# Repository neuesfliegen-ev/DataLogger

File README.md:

# 🛩️ Flight Data Logger

This project is a **Flight Data Logger** designed for UAVs and model aircraft. It logs sensor and GPS data at 1 Hz to an SD card in CSV format and streams live telemetry to a server over a cellular (3G/4G) link. The system uses an IMU, a barometric sensor and a GPS module, and shows live status updates on an OLED screen.

## 📦 Features

- Logs data to SD card in `.csv` format
- Captures:
  - 9-axis IMU data (acceleration, gyroscope, magnetometer)
  - Barometric pressure, altitude and temperature
  - GPS coordinates, altitude, speed and satellite count
- OLED display for live status updates
- **Live telemetry over cellular**: an ESP32 gateway forwards data to a web server through a SIM7600 modem (see [Live Telemetry](#-live-telemetry-esp32--sim7600))
- Live dashboard for the telemetry data
- Modular and extensible design for future sensor integration

## 🧠 Core Components

| Component           | Description |
|---------------------|-------------|
| **Arduino**         | Primary microcontroller (Nano 33 BLE Sense REV2): sensors, SD logging, OLED |
| **ESP32**           | Telemetry gateway between the Arduino and the cellular modem |
| **SIM7600**         | Cellular modem (with SIM card), controlled by AT commands over UART |
| **BMI270_BMM150**   | 9-DOF IMU (acceleration, gyroscope, magnetometer) |
| **LPS22HB**         | Barometric pressure sensor |
| **TinyGPS++**       | GPS data parser |
| **SH1106 OLED**     | I2C 128x64 screen for live feedback |
| **SD Card Module**  | Stores `.csv` data logs |
| **Voltage Divider** | Scales down battery voltage for safe ADC reading |

---

## 📡 Live Telemetry (ESP32 + SIM7600)

Code: [`esp32SimNano.ino`](esp32SimNano.ino)

```
Arduino Nano ──I2C (JSON frames)──► ESP32 ──UART (AT commands)──► SIM7600 ──HTTP POST──► Server ──► Dashboard
     ▲                                │
     └────── READY / ACK (GPIO) ──────┘
```

- **Arduino → ESP32:** the ESP32 runs as an I2C slave (address `0x42`) and receives each data frame as a JSON payload.
- **Handshake:** two GPIO lines coordinate the transfer:
  - `READY` (ESP32 → Nano, GPIO 4): high when the modem is up and the ESP32 can accept a new frame.
  - `ACK` (ESP32 → Nano, GPIO 5): high when the last frame was delivered successfully (HTTP 200).
- **ESP32 → SIM7600:** UART2 at 115200 baud (ESP32 TX = GPIO 17, RX = GPIO 16). On startup the ESP32:
  1. waits until the modem answers `AT`
  2. disables echo (`ATE0`)
  3. opens the network (`AT+NETOPEN`)
  4. starts an HTTP session (`AT+HTTPINIT`, recovering with `AT+HTTPTERM` if a session is stuck)
  5. sets the server URL and `application/json` content type (`AT+HTTPPARA`)
- **Sending:** each frame is uploaded with `AT+HTTPDATA` and sent as an HTTP POST (`AT+HTTPACTION=1`). The ESP32 then waits for an HTTP 200 response.
- **Health check:** the ESP32 polls the modem with `AT` every 200 ms and updates the `READY` line.
- **Modes:** the payload carries a `"mode"` field (`REALTIME` or `BATCH`), which the ESP32 parses.

---

## 🔧 Circuit Diagram

[Wiring diagram](Datenlogger_Files/Datalogger_schematic%20v2.pdf)

> Note: the schematic still shows a 430 Ω resistor in the voltage divider. Use **510 Ω** as described below.

---

## 🔋 ADC Voltage Divider

To safely read the battery voltage with the Arduino's 3.3 V ADC pin, use the following voltage divider:

- **Input voltage**: up to 4.2 V (LiPo 1S max)
- **Top resistor (battery side)**: 510 Ω
- **Bottom resistor (to GND, ADC reads across it)**: 1.8 kΩ

### 📐 Voltage Divider Calculation

```
Vout = Vin × R_bottom / (R_top + R_bottom)
     = 4.2 V × 1800 / (510 + 1800)
     ≈ 3.27 V
```

---

## 📂 Data Format

Logged data is stored as a CSV file (`log.csv`) with the following headers:

```
timestamp,accX,accY,accZ,gyroX,gyroY,gyroZ,magX,magY,magZ,
latitude,longitude,gpsAltitude,Speed,SatCount,roll,pitch,yaw,
pressure,temperature,paltitude
```

Example row:

```
1542,-0.01,0.02,9.81,0.01,-0.02,0.00,30.12,11.23,-45.66,
52.5200,13.4050,120.5,10.4,9,0,0,0,100.3,25.5,132.2
```

---

## 🛠️ Getting Started

### 🔌 Wiring

- Connect sensors and modules via I2C/SPI/Serial as per the diagram.
- Ensure GPS is connected to `Serial1` (typically `TX`/`RX` on the Arduino). (IMPORTANT)
- For telemetry: connect the Arduino to the ESP32 over I2C plus the `READY`/`ACK` lines, and the ESP32 to the SIM7600 over UART (pins above). Insert an active SIM card.
- Insert a **FAT32-formatted SD card**.

### 🧪 Uploading

1. Install dependencies (Arduino):
   - `Arduino_BMI270_BMM150`
   - `Arduino_LPS22HB`
   - `TinyGPSPlus`
   - `U8g2`
2. Compile and upload the main sketch to the Arduino.
3. Upload `esp32SimNano.ino` to the ESP32 (ESP32 board package, uses `Wire` and `HardwareSerial`). Set the server URL in `initSIM7600()` if needed.
4. Open the Serial Monitor at **115200 baud** to see real-time debug info (the ESP32 also echoes modem responses there).

---

## 📊 OLED Display

The OLED shows system status:
- Sensor initialization
- GPS satellite count
- Errors during SD or sensor setup
- Team number

> To keep the display clear and reduce power, messages are brief and limited to startup and GPS updates.

---

## 🧩 Planned Improvements

- Add orientation calculation (roll, pitch, yaw)
- Support logging at configurable rates (5 Hz, 10 Hz)
- Add battery voltage and current sensors

---

## 👨‍💻 Credits

- Developed by the **Neues Fliegen Avionics Team**
- Based on libraries by Arduino, Adafruit and Mikal Hart (TinyGPS++)

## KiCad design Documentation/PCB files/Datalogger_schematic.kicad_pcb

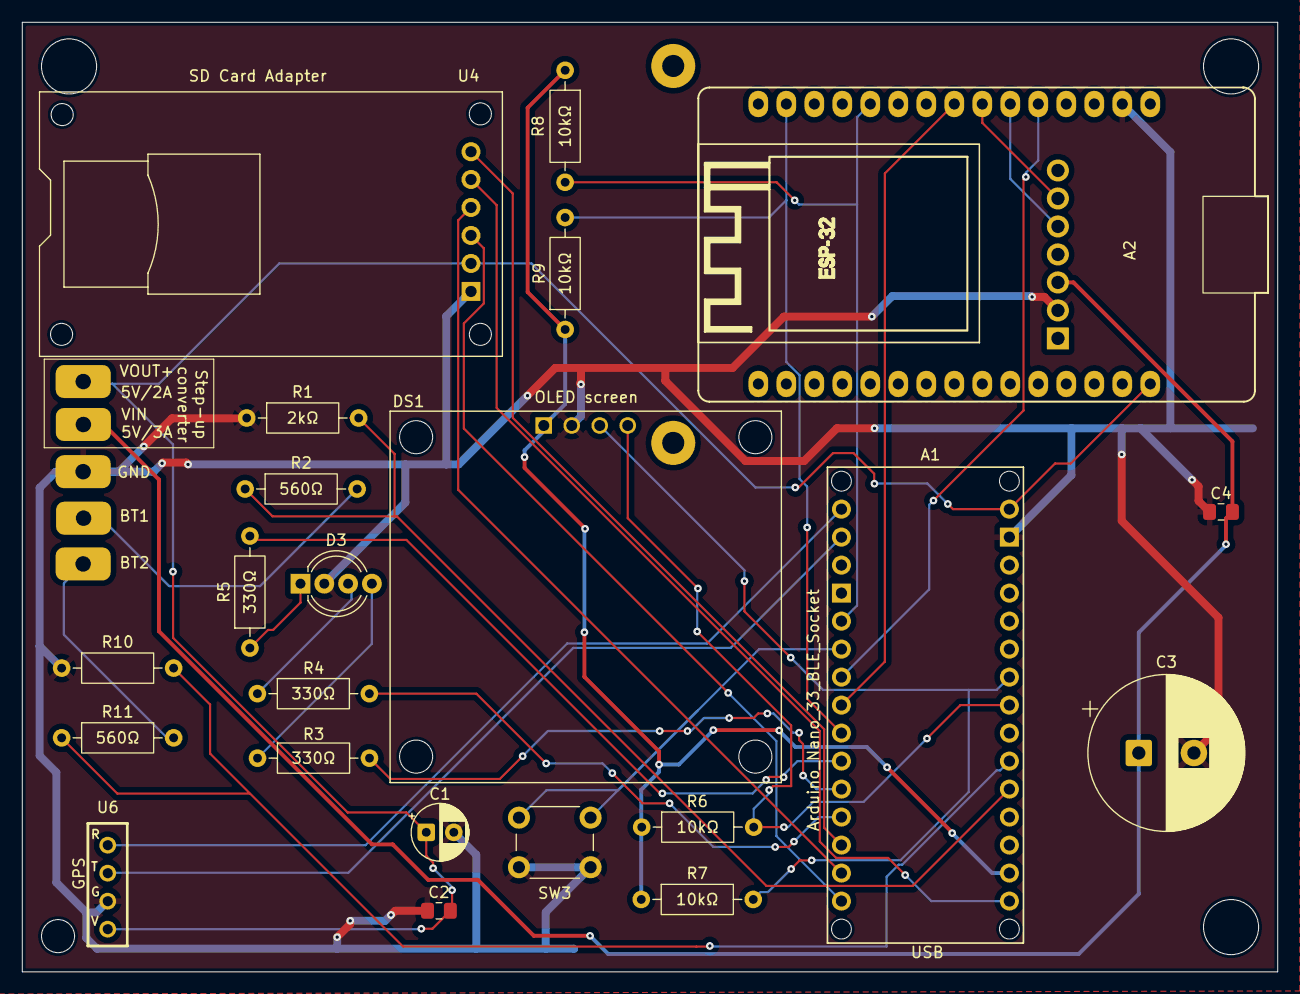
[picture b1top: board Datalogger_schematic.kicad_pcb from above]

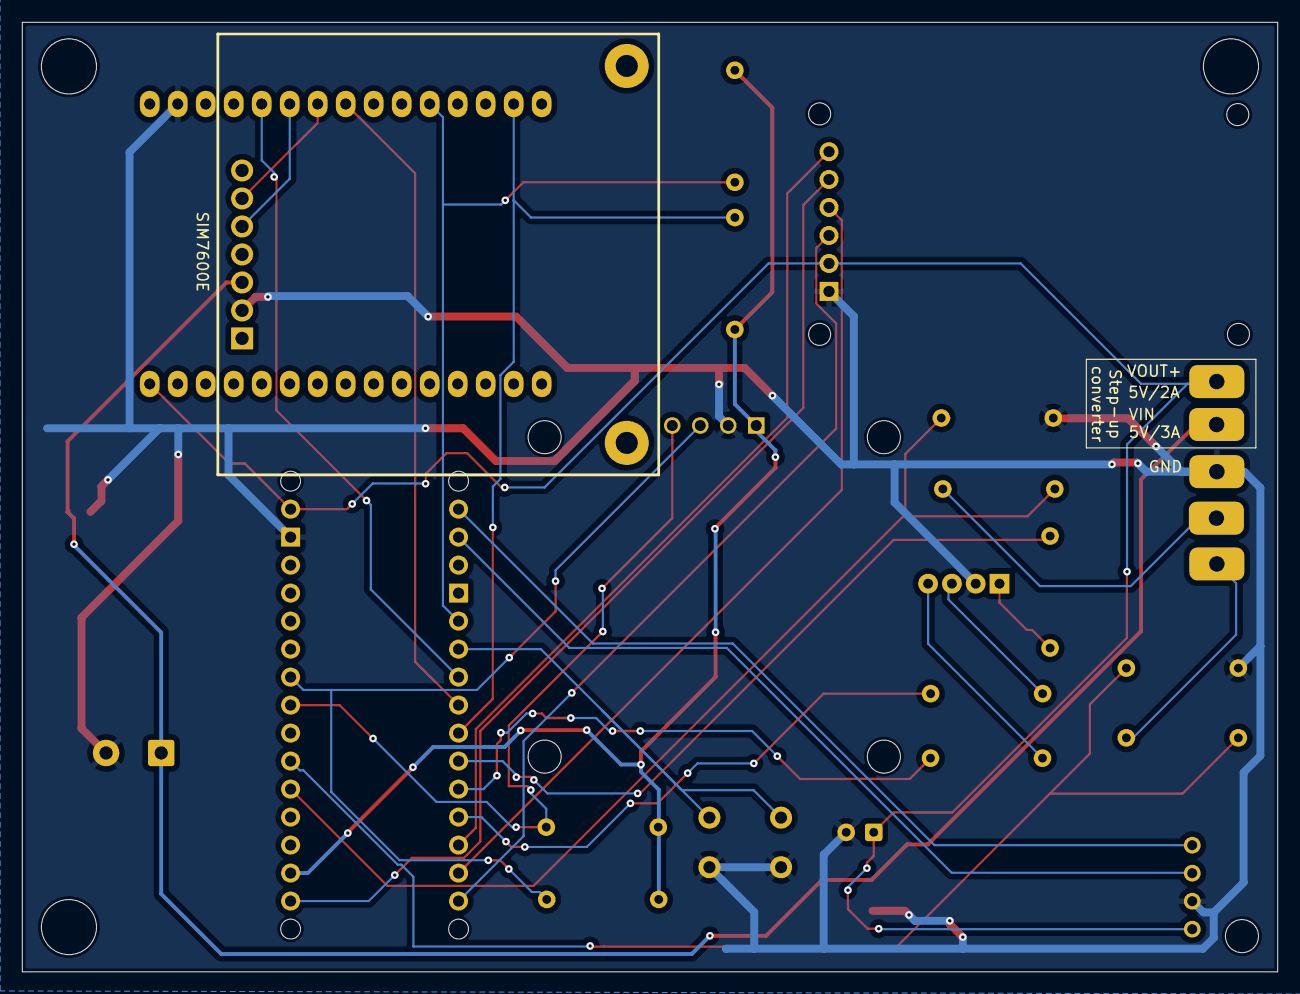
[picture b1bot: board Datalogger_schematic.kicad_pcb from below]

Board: 2 copper layers, 113.9 x 86.2 mm, 26 parts (2 on the bottom side), 29 nets.

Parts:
A1: Arduino_Nano_33_BLE_Socket; Arduino_Nano_Every_Socket
A2: ESP32_DevKit_V1_DOIT_30GPIOs; DOIT_ESP32_DEVKIT_30Pins
BT1, BT2: Battery_Cell; Battery single pin
C1: 330uF/10V; CP_Radial_D5.0mm_P2.50mm
C2, C4: 100nF_Ceramic/10V; C_0805_2012Metric_Pad1.18x1.45mm_HandSolder
C3: 1000uF/10V; CP_Radial_D14.0mm_P5.00mm
D3: APA-106-F5; LED_D5.0mm-4_RGB_Wide_Pins
DS1: OLED_128X64_1.3_I2C; LCD_OLED_128X64_1.3_I2C
R1, R2, R3, R4, R5, R10, R11: Resistor; R_Axial_DIN0207_L6.3mm_D2.5mm_P10.16mm_Horizontal
R6, R7, R8, R9: 10k; R_Axial_DIN0207_L6.3mm_D2.5mm_P10.16mm_Horizontal
SW3: Push_Button; SW_PUSH_6mm
U2: MT3608-Module
U4: Micro_SD_Card_Module
U5: SIM7600E
U6: GPS6PIN

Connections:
3.3V: A1.3V3 (3.3V), DS1.1 (VDD), R6.1, R7.1, R8.1, R9.1
5V/2A: A1.VIN, A2.30 (VIN), C1.1, C2.2, U2.3 (Vout+), U4.5 (VCC), U6.1 (5V)
5V/3A: C3.1, C4.2, U5.5 (VCC)
GND: A1.GND2 (GND), A2.2 (GND), C1.2, C2.1, C3.2, C4.1, D3.2 (GND), DS1.2 (GND), R1.1, R10.1, SW3.2, U4.6 (GND), U5.6 (GND), U6.2 (GND)
unnamed: A1.A4 (A4/SDA), DS1.4 (SDA), R6.2
unnamed: A1.A5 (A5/SCL), DS1.3 (SCK), R7.2
unnamed: A1.D0 (D0/RX), U6.3 (TX)
unnamed: A1.D1 (D1/TX), U6.4 (RX)
unnamed: A1.D11 (D11_MOSI), U4.3 (MOSI)
unnamed: A1.D12 (D12_MISO), U4.4 (MISO)
unnamed: A1.D13 (D13_SCK), U4.2 (SCK)
unnamed: A1.A1, R1.2, R2.1
unnamed: A1.A2, R10.2, R11.1
unnamed: A1.D3, SW3.1
unnamed: A1.D7, R5.2
unnamed: A1.D8, R3.2
unnamed: A1.D9, R4.2
unnamed: A1.D4, A2.5 (D4/ADC2_CH0)
unnamed: A1.D5, A2.8 (D5)
unnamed: A1.D2, A2.11 (D21/SDA), R8.2
unnamed: A1.D6, A2.14 (D22/SCL), R9.2
unnamed: A2.6 (RX2/GPIO16), U5.3 (TX)
unnamed: A2.7 (TX2/GPIO17), U5.2 (RX)
unnamed: BT1.1 (+), R2.2
unnamed: BT2.1 (+), R11.2
unnamed: D3.4 (DI), R3.1
unnamed: D3.1 (DO), R5.1
unnamed: D3.3 (VDD), R4.1
unnamed: A1.D10, U4.1 (CS)

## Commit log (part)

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2025-05-26 Update and rename pre_final.ino to DataLogger_2025.ino
    Renaming and small cosmatics edits
2025-05-28 Add wiring diagram
    Missing step-up converter connections to Arduino.
2025-05-28 Add wiring diagram to README.md
2025-05-28 Update wiring diagram
    Changes to step-up converter and R2 connections.
2025-05-28 Update README
    Update wiring diagram link in README
2025-05-30 Uploaded initial documentation
2025-05-31 Update DataLogger_2025.ino
    Added:
    - calibrateIMU() function
    - Global variables for sensor's offsets
    - Included calibrateIMU() inside IMU's initialization in setup() function
2025-05-31 Update README.md
    Warning added to the ADC Voltage Divider. Proposal to change the values of the resistances.
2025-05-31 Update DataLogger_2025.ino
    - Update functions for OLED display.
    - Add loop to OLED display after initiation.
    - Add global variable for battery level.
2025-06-01 Update DataLogger_2025.ino
    Revisions to the calibrationIMU() function:
    - sum parameters are now local
    - accZ_off is corrected to account for its initial value
    - delay(2000ms) changed to 25ms
    - included preAcc and preGyro parameters
    For future expansion, I would be excited to work with task synchronization techniques, to avoid ISR interruptions.
2025-06-01 Add button and battery check functions DataLogger_2025.ino
    Added button which starts/stop data logging at release.
    Removed delay() from loop() because data logging frequency is determined by new global constant.
    Removed SD.open() and dataFile.close() from logToSD() because start/stop logging functions respectively open and close the file.
    Battery checking function turns on red LED when charging is needed and green LED when charging is sufficient. Updates global variable batteryVoltage and LED indication every loop.
2025-06-04 Create Boring Notes
2025-06-05 Update Boring Notes
2025-06-06 Update wiring diagram
    - Add LEDs circuit part.
    - Add capacitors for SD card reader.
    - Add common Ground and common Vcc lines for components.
    - Modify voltage divider resistance value.
2025-06-06 Update README
    - Update attached link to wiring diagram.
2025-06-09 First Day's Work
    Code after first day. Still testing out different kernels and window sizes. More to come
2025-06-11 Update DataLogger_2025.ino
    Median Filter implemented for calibration of the IMU.
    Next steps:
    - Calibrating the Magnetometer (this week)
    - Improving the reliability taking ISR interruptions into account. Once this point is achieved for key code areas, display messages can be removed saving initialization time.
    What's a median filter and why using it improves the performance?
    Example:
2025-06-16 Uploaded "A03 Magnetometer Analysis"
    Using sample data from public flights, an offline Kalman Filter is tested to remove hard-iron and soft-iron offsets from the magnetometer. It is the stepstone of a final version that will be used to 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
    This program must be tested using different positions of the plane to understand what is the most efficient calibration procedure. Possible alternatives include:
    - Real-time calibration (doesn't seem the most effective, proven in this data study)
    - 360 degrees rotations before the start of the flight (potential solution)
    - 3D 360 degrees rotations (unpractical for medium size planes)
2025-06-18 Convolution Filter Testing
    Testing different ways to handle the edges for the convolution filter. Test_4.py and Test_5.py are promising
2025-06-18 Update calibration program in .ino
    Polished my previous commit regarding the IMU calibration:
    - Fixed inefficiencies such as the offsets calculated inside the loop
    - Fixed the variable name mistake in accXCalibBuffer[CALIB_SAMPLES];
    - Avoided a busy-loop in "while (!IMU.accelerationAvailable() || !IMU.gyroscopeAvailable())"
    - Fixed two typos in "while(!IMU.accelerationAvailable() || !IMU.gyroscopeAvailable()));"
    Potential future patches:
2025-06-19 Updating window_size var
    Added the variable window_size to easily compare the effects of adjusting the window size
2025-06-19 Create Test_6.py
    Created Test_6.py to show the same convolution method as in Test_4.py and Test_5.py but with the offset being removed.
    A small mistake was also fixed in Test_5.py
2025-06-20 Test_7.py + Test_8.py + Minor updates
    - Created Test_7.py
    - Created Test_8.py
    - Fixed small logic mistakes
2025-06-22 Update DataLogger_2025.ino
    Shiro: new data logger version
    -- Luciano´s imu calibration included
    -- interrupt of the button implemented
    -- gps ready state added
    -- logging state update
2025-06-27 Allows repo management from Visual Studio
2025-06-27 Final MATLAB Magnetometer analysis + restructured folders and README files
2025-06-27 Updated README files
2025-06-28 Calibration methods: Full Kalman / Six-Axis / Two-Axis
2025-06-28 Update DataLogger_2025.ino Magnetometer Calibration
    Magnetometer calibration program assuming we use a Two-Axis calibration procedure (all described inside the MATLAB folder).
    I will continue adding refinements during the week.
2025-07-17 Create esp32SimNano.ino
    This is a new firmware to the esp32 module. this module is sued to receive the data from arduino nano over I2C as chunks. then send it to sim7600 to the server
2025-07-18 Update DataLogger_2025.ino
    adding the missing semi column from the last PR!
2025-08-04 Completed implementation of Gaussian and Softmax GPS filters.
    Test 10 - Program to simulate live sensor data and feed into Gaussian filter.
    Test 11 - Program to simulate live GPS sensor data and feed into Softmax GPS filter.
    TimeTest - Program to measure performance of both filters.
2025-08-05 Simplified magnetometer test program update: adapted to current commits and enhanced logic
2025-08-05 Magnetometer test-program update
2025-08-06 Update .ino (Magnetometer calibration)
    Completed the Magnetometer calibration, prepared for 6-Axis method. After calibration, magX, magY, magZ are NOT zero.
    - Included constants, such as "CALIB_SAFETY_CHECK", logic and functions for debugging and quality-check purposes.
    @Shiro-01, the code was tested on a simplified version, although I couldn't run the whole application due to the <CircularBuffer.hpp> dependency. Everything should work as expected in the complete pr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
    Future steps:
    - Calculate roll, yaw, and pitch and make sure the readings are reliable after calibration (I'm very interested on inspecting this).
    - Consider a Kalman real-time filter to account for the distortio
2025-08-06 Update .ino: BATCH Mode Robustness
    Further error handling in BATCH mode, and suggested improvements.
2025-08-07 Create PCB folder
2025-08-07 Add files via upload
    - Add PCB project files.
    - Add front and back images of 3D view of PCB model.
2025-08-07 Add files via upload
    - Add new version of schematic.
2025-08-07 Update DataLogger_2025.ino
    - Edited view of messages shown in OLED screen.
2025-08-07 Update README.md
    - Update schematic.
2025-08-08 Update DataLogger_2025.ino
    Adding ESP comunicatoin protocol with error handling.
2025-08-13 Updated simplified application to work with BLE handlers
2025-08-13 Bluetooth Control
    @Shiro-01 I attach you as a reviewer of this commit for you to test the program with the full prototype. However, the changes are done mostly in a safe way with the use of the macro "WITH_BLUETOOTH",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
    The code implements BLE functionalities without the use of the mentioned RemoteXY library, which would interfere with some natural RTOS functions. A downside may be limited GUI, but this achieves sim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
    How to connect with the program?
    1) Download "nRF Connect" compatible with iOS and Android
    2) Connect with de
2025-08-14 Modularization of DataLogger_2025.ino for better maintainability and future expansion. (Still to be tested with the complete prototype)
2025-08-16 Update DataLogger_2025.ino
    adding wrap with filename to data being uploaded to cloud
2025-08-16 Test program update
2025-08-16 Main program update: Simplified attitude calculation
    Well working program, using simple sensor fusion logic. Achieves the expected results.
2025-08-19 Main program: BLE raw logic removal
    Implementation of RemoteXY will take place
2025-08-19 Libraries update
2025-08-19 Update esp32SimNano.ino
    adding remotexy
2025-08-19 Revert "Update esp32SimNano.ino"
    This reverts commit 53f1844ccb404ec4c66f032d9cbfcc5e10778e0f.
2025-08-19 Update test program
2025-08-20 Main program: On-device Kalman FiIlter
2025-08-20 Main program: Kalman Filter + Payload update
2025-08-20 Necessary libraries for on-device Kalman Filter
    Source: https://github.com/TKJElectronics/KalmanFilter
    In order to run in the Arduino IDE, change from #include <Kalman.h> to #include "Kalman.h"
2025-08-20 Main program: BLE logic
2025-08-26 Digital Flight Tracker for post-competion evaluation
2025-08-26 Digital Flight Tracker for post-competion evaluation (2)
2025-08-26 Digital Flight Tracker for post-competion evaluation (3)
2025-08-26 Digital Flight Tracker for post-competion evaluation (4)
2025-10-24 Datalogger schematic
    - Add updated schematic
2025-10-24 Create folder
    Create folder for PCB files
2025-10-24 Upload files
    Upload datalogger project files
